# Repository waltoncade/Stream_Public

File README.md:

# Stream
READ THE SHIT OUTTA ME

#Twitch
reflectwin channel_id = 153781693

#Necessary Packages
- pynput
- pyqt5

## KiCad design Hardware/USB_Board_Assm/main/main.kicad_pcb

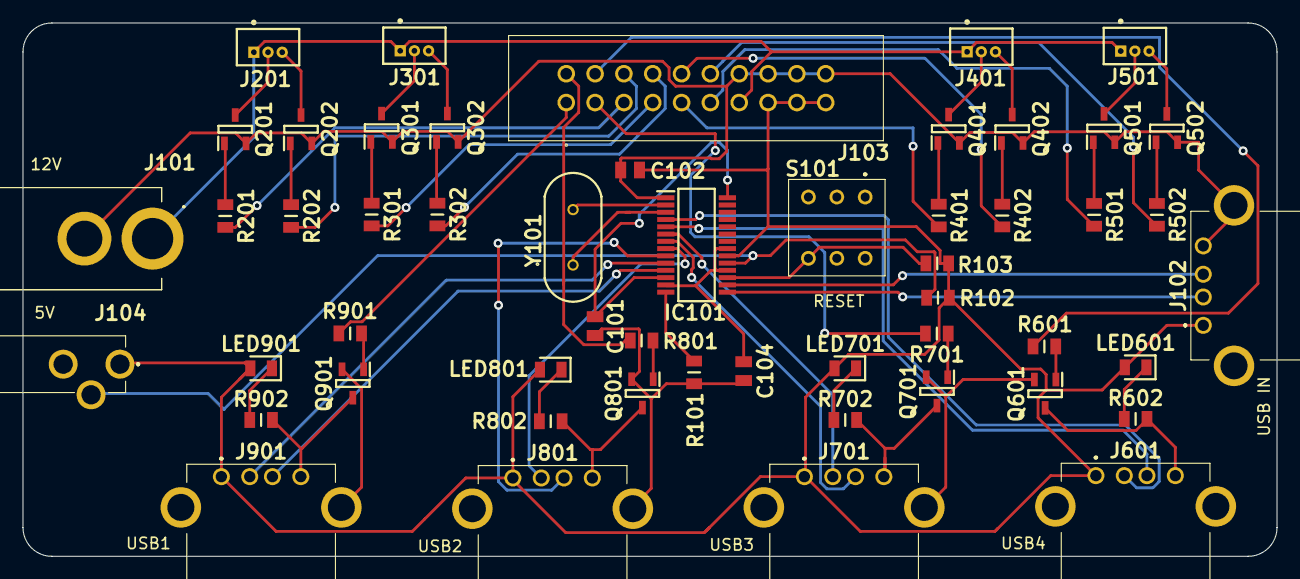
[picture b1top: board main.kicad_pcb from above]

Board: 2 copper layers, 110.5 x 47.0 mm, 53 parts (0 on the bottom side), 60 nets.

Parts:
C101, C102, C104: GRM21BC81D106KE51L; CAPC2012X145N
IC101: FE1.1S; SOP64P600X175-28N
J101: PJ-037A; PJ037A
J102, J601, J701, J801, J901: USB-A1HSW6; USBA1HSW6
J103: TST-110-01-G-D; TST-110-XX-Y-D
J104: PJ-031DH; PJ031DH
J201, J301, J401, J501: 0530470310; SHDRV3W50P0_125_1X3_550X320X420P
LED601, LED701, LED801, LED901: VFHR1112H-3BY2A-TR; LEDC2012X90N
Q201, Q202, Q301, Q302, Q401, Q402, Q501, Q502, Q601, Q701, Q801, Q901: AO3414; SOT95P280X125-3N
R101, R102, R103: RK73H2ATTD2701F; RESC2012X60N
R201, R202, R301, R302, R401, R402, R501, R502, R601, R701, R801, R901: RK73B2ATTD221J; RESC2012X60N
R602, R702, R802, R902: RK73B2ATTD151J; RESC2012X60N
S101: TL2201EEYA
Y101: ECS-120-20-4; HC-49USX

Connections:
+5V: C102.2, IC101.20, J102.1, J103.15, J103.17, J103.19, J104.1, J601.1, J701.1, J801.1, J901.1, LED601.2, LED701.2, LED801.2, LED901.2, R102.1, R103.1
+12V: J101.1, J103.13, J201.1, J301.1, J401.1, J501.1
/D0+: IC101.16, J102.3
/D1+: IC101.11, J901.3
/D1-: IC101.10, J901.2
/D2+: IC101.9, J801.3
/D2-: IC101.8, J801.2
/D3+: IC101.7, J701.3
/D3-: IC101.6, J701.2
/D4+: IC101.5, J601.3
/D4-: IC101.4, J601.2
/DO-: IC101.15, J102.2
/L1G: J103.5, R201.1
/L1R: J103.6, R202.1
/L2G: J103.7, R301.1
/L2R: J103.8, R302.1
/L3G: J103.9, R401.1
/L3R: J103.10, R402.1
/L4G: J103.11, R501.1
/L4R: J103.12, R502.1
/USB1: J103.1, R901.1
/USB2: J103.2, R801.1
/USB3: J103.3, R701.1
/USB4: J103.4, R601.1
/VD18: C101.2, IC101.12, IC101.28
/VD33: C104.2, IC101.13, IC101.18, IC101.21
GND: C101.1, C102.1, C104.1, IC101.1, J101.2, J102.4, J102.6, J103.14, J103.16, J103.18, J103.20, J104.2, J601.6, J701.6, J801.6, J901.6, Q201.2, Q202.2, Q301.2, Q302.2, Q401.2, Q402.2, Q501.2, Q502.2, Q601.2, Q701.2, Q801.2, Q901.2, R101.2, S101.5
unnamed: IC101.2, Y101.2
unnamed: IC101.3, Y101.1
unnamed: IC101.14, R101.1
unnamed: IC101.17, R103.2, S101.6
unnamed: IC101.19, J104.3, R102.2
unnamed: J201.2, Q201.3
unnamed: J201.3, Q202.3
unnamed: J301.2, Q301.3
unnamed: J301.3, Q302.3
unnamed: J401.2, Q401.3
unnamed: J401.3, Q402.3
unnamed: J501.2, Q501.3
unnamed: J501.3, Q502.3
unnamed: J601.4, Q601.3, R602.1
unnamed: J701.4, Q701.3, R702.1
unnamed: J801.4, Q801.3, R802.1
unnamed: J901.4, Q901.3, R902.1
unnamed: LED601.1, R602.2
unnamed: LED701.1, R702.2
unnamed: LED801.1, R802.2
unnamed: LED901.1, R902.2
unnamed: Q201.1, R201.2
unnamed: Q202.1, R202.2
unnamed: Q301.1, R301.2
unnamed: Q302.1, R302.2
unnamed: Q401.1, R401.2
unnamed: Q402.1, R402.2
unnamed: Q501.1, R501.2
unnamed: Q502.1, R502.2
unnamed: Q601.1, R601.2
unnamed: Q701.1, R701.2
unnamed: Q801.1, R801.2
unnamed: Q901.1, R901.2

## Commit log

2020-11-13 Public
2020-11-26 Here you go J
2020-12-01 instanciated face detection thread
    -Extended basic thread object
    -Paramterized the FaceDetetion
    -Face Manipulation methods
2021-01-03 dummy thicc commit for the bois
